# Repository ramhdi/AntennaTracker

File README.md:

# TrackerAntenna

Tracker Antenna - a device of Aksantavirya - Aksantara ITB team

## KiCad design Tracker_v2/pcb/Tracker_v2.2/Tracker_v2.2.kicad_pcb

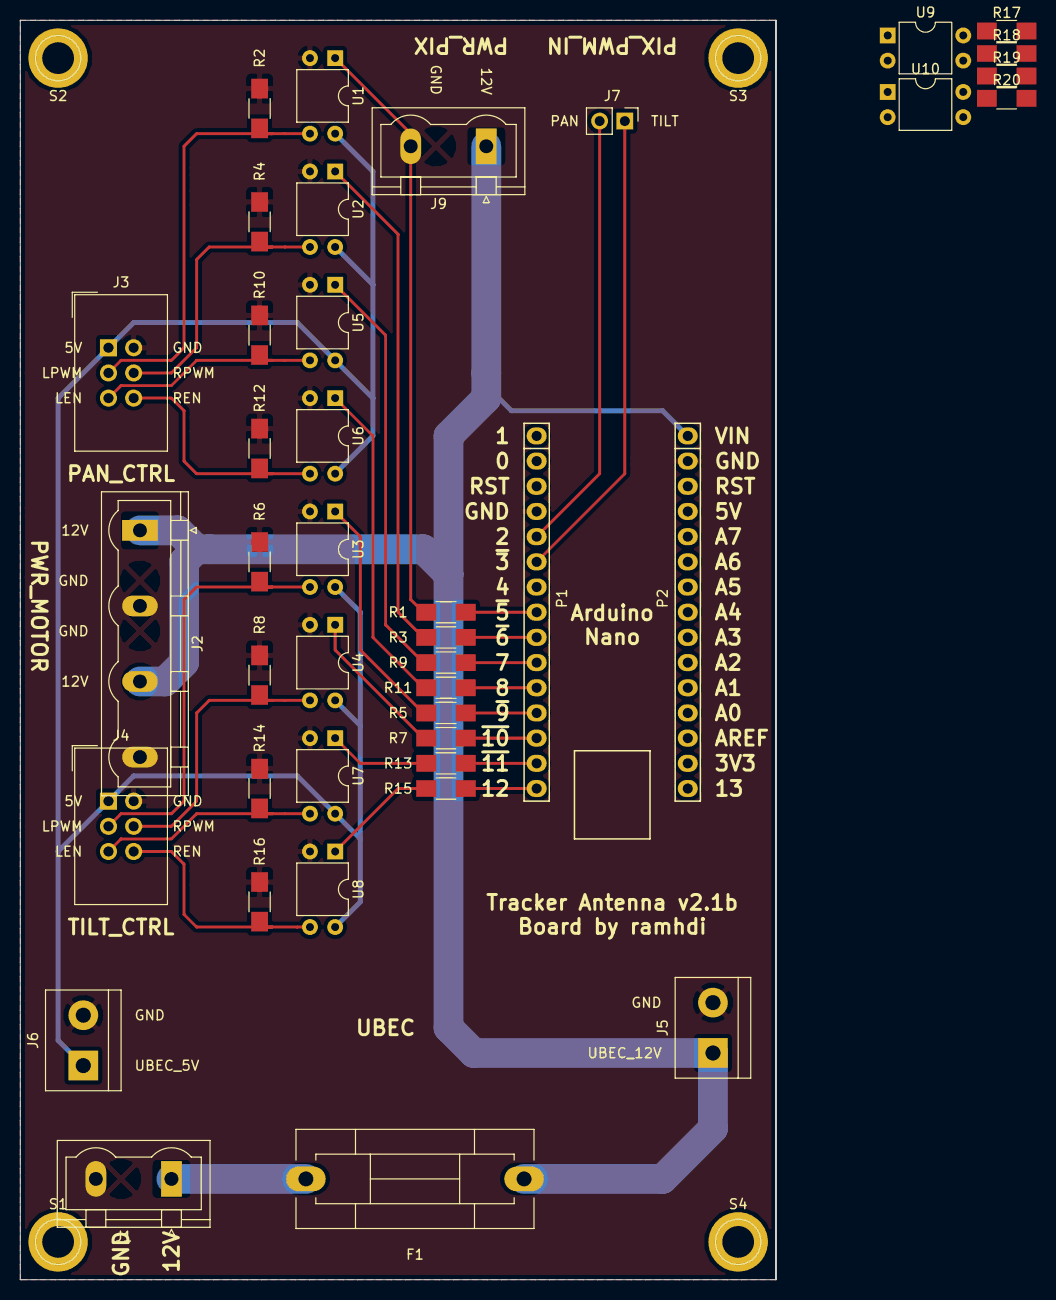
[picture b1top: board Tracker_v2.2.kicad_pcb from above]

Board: 2 copper layers, 76.2 x 127.0 mm, 45 parts (0 on the bottom side), 35 nets.

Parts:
F1: Fuse; Fuseholder5x20_horiz_SemiClosed_Casing10x25mm
J1: Vin_12V; PhoenixContact_GMSTBVA-G_02x7.62mm_Vertical
J2: Motor_12V; PhoenixContact_GMSTBVA-G_04x7.62mm_Vertical
J3: Pan_Ctrl; IDC-Header_2x03_P2.54mm_Vertical
J4: Tilt_Ctrl; IDC-Header_2x03_P2.54mm_Vertical
J5: BEC_IN_12V; TerminalBlock_bornier-2_P5.08mm
J6: BEC_OUT_5V; TerminalBlock_bornier-2_P5.08mm
J7: PIX_PWM_IN; Pin_Header_Straight_1x02_Pitch2.54mm
J9: Vout_12V; PhoenixContact_GMSTBVA-G_02x7.62mm_Vertical
P1: Digital; Socket_Strip_Arduino_1x15
P2: Analog; Socket_Strip_Arduino_1x15
R1, R2, R3, R4, R5, R6, R7, R8, R9, R10, R11, R12, R13, R14, R15, R16, R17, R18, R19, R20: 1k; R_1206_HandSoldering
S1, S2, S3, S4: 1pin
U1, U2, U3, U4, U5, U6, U7, U8, U9, U10: TLP785; DIP-4_W7.62mm

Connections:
+5V: J3.1, J4.1, J6.1, U1.4, U2.4, U3.4, U4.4, U5.4, U6.4, U7.4, U8.4, U9.4, U10.4
+12V: F1.1, J2.1, J2.4, J5.1, J9.1, P2.1
/Reset: P1.3, P2.3
GND: J1.2, J2.2, J2.3, J3.2, J4.2, J5.2, J6.2, J9.2, P1.4, P2.2, R2.1, R4.2, R6.1, R8.2, R10.1, R12.2, R14.1, R16.2, R18.1, R20.2, U1.2, U2.2, U3.2, U4.2, U5.2, U6.2, U7.2, U8.2, U9.2, U10.2
unnamed: F1.2, J1.1
unnamed: R1.1, U1.1
unnamed: R3.2, U2.1
unnamed: R5.1, U3.1
unnamed: R7.2, U4.1
unnamed: R9.1, U5.1
unnamed: R11.2, U6.1
unnamed: R13.1, U7.1
unnamed: R15.2, U8.1
unnamed: R17.1, U9.1
unnamed: R19.2, U10.1
PAN_L_EN: P1.10, R9.2
PAN_L_EN_ISOL: J3.5, R10.2, U5.3
PAN_L_PWM: P1.8, R1.2
PAN_L_PWM_ISOL: J3.3, R2.2, U1.3
PAN_PWM_IN: J7.2, R17.2
PAN_PWM_IN_ISOL: P1.5, R18.2, U9.3
PAN_R_EN: P1.11, R11.1
PAN_R_EN_ISOL: J3.6, R12.1, U6.3
PAN_R_PWM: P1.9, R3.1
PAN_R_PWM_ISOL: J3.4, R4.1, U2.3
TILT_L_EN: P1.14, R13.2
TILT_L_EN_ISOL: J4.5, R14.2, U7.3
TILT_L_PWM: P1.12, R5.2
TILT_L_PWM_ISOL: J4.3, R6.2, U3.3
TILT_PWM_IN: J7.1, R19.1
TILT_PWM_IN_ISOL: P1.6, R20.1, U10.3
TILT_R_EN: P1.15, R15.1
TILT_R_EN_ISOL: J4.6, R16.1, U8.3
TILT_R_PWM: P1.13, R7.1
TILT_R_PWM_ISOL: J4.4, R8.1, U4.3

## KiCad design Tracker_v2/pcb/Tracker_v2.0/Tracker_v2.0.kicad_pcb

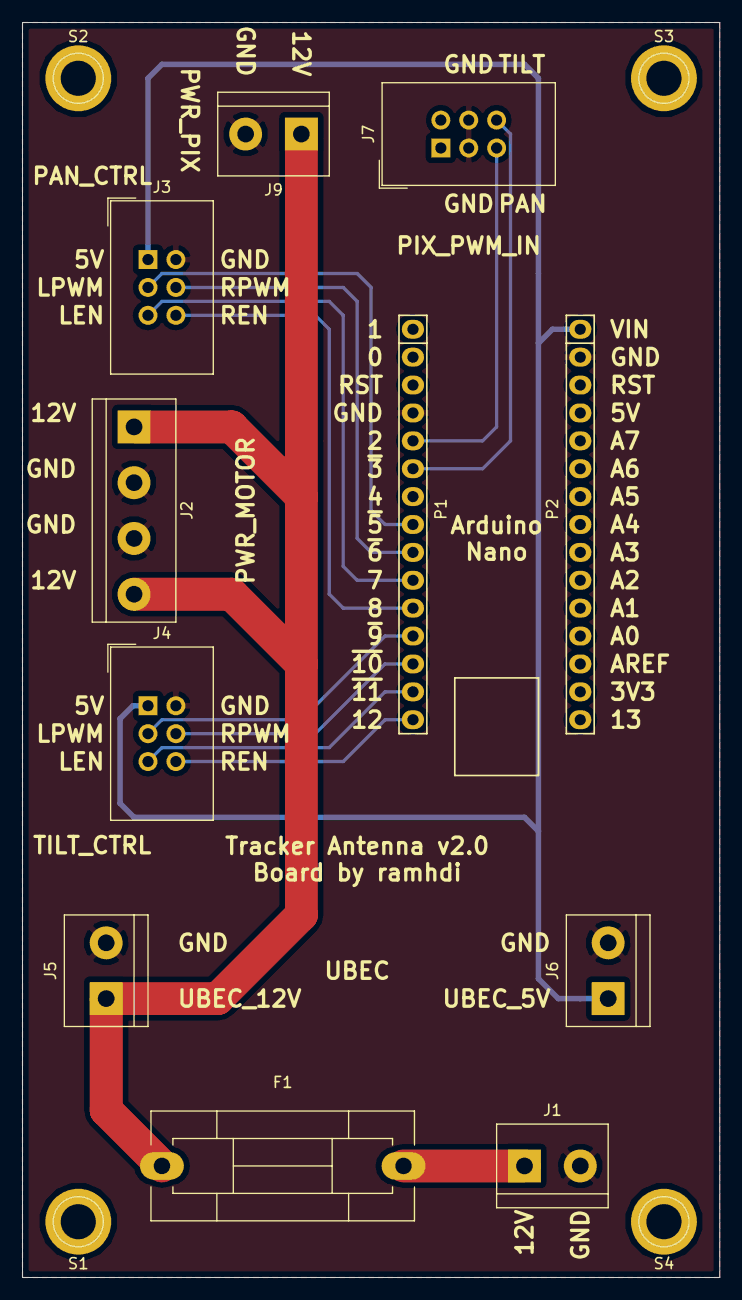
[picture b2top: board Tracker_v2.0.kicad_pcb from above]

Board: 2 copper layers, 63.5 x 114.3 mm, 15 parts (0 on the bottom side), 15 nets.

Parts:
F1: Fuse; Fuseholder5x20_horiz_SemiClosed_Casing10x25mm
J1: Vin_12V; TerminalBlock_bornier-2_P5.08mm
J2: Motor_12V; TerminalBlock_bornier-4_P5.08mm
J3: Pan_Ctrl; IDC-Header_2x03_P2.54mm_Vertical
J4: Tilt_Ctrl; IDC-Header_2x03_P2.54mm_Vertical
J5: BEC_IN_12V; TerminalBlock_bornier-2_P5.08mm
J6: BEC_OUT_5V; TerminalBlock_bornier-2_P5.08mm
J7: Pix_PWM_In; IDC-Header_2x03_P2.54mm_Vertical
J9: Vout_12V; TerminalBlock_bornier-2_P5.08mm
P1: Digital; Socket_Strip_Arduino_1x15
P2: Analog; Socket_Strip_Arduino_1x15
S1, S2, S3, S4: 1pin

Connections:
+5V: J3.1, J4.1, J6.1, P2.1
+12V: F1.1, J2.1, J2.4, J5.1, J9.1
/Reset: P1.3, P2.3
GND: J1.2, J2.2, J2.3, J3.2, J4.2, J5.2, J6.2, J7.3, J7.4, J9.2, P1.4, P2.2
unnamed: F1.2, J1.1
PAN_L_EN: J3.5, P1.10
PAN_L_PWM: J3.3, P1.8
PAN_PWM_IN: J7.5, P1.5
PAN_R_EN: J3.6, P1.11
PAN_R_PWM: J3.4, P1.9
TILT_L_EN: J4.5, P1.14
TILT_L_PWM: J4.3, P1.12
TILT_PWM_IN: J7.6, P1.6
TILT_R_EN: J4.6, P1.15
TILT_R_PWM: J4.4, P1.13

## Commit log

2018-12-06 Add new directory
2018-12-06 Upload New File
2018-12-07 Added more versions of PCBs and codes
2019-02-25 Removed PCB files
